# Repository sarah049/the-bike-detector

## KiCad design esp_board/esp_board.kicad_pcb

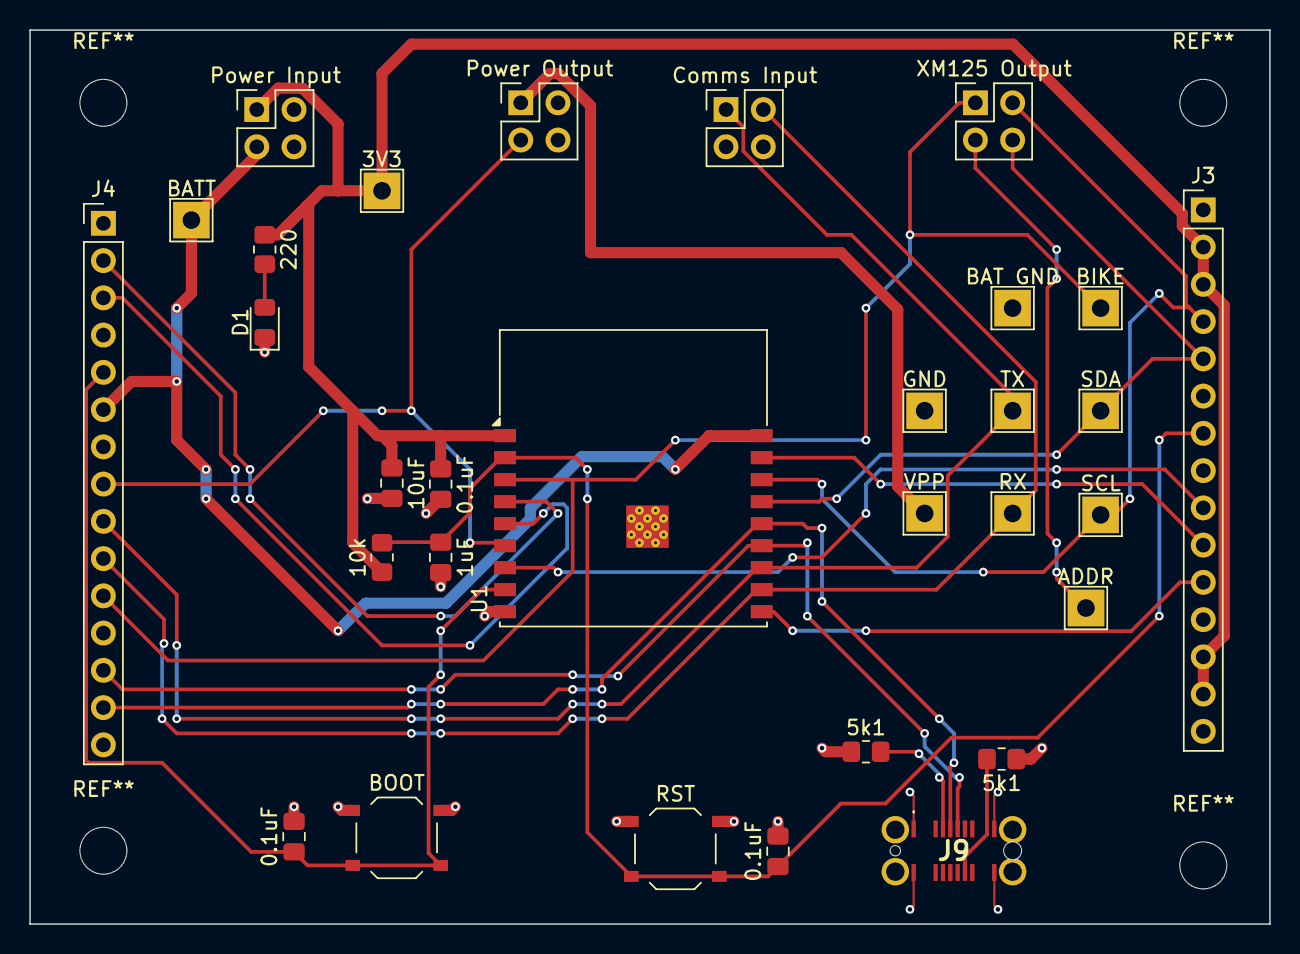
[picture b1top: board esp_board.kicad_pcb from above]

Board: 2 copper layers, 84.5 x 61.0 mm, 31 parts (0 on the bottom side), 23 nets.

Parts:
0.1uF, 0.1uF#2, 0.1uF#3: 0.1uF; C_0805_2012Metric_Pad1.18x1.45mm_HandSolder
1uF: 1uF; C_0805_2012Metric_Pad1.18x1.45mm_HandSolder
3V3: 3V3; TestPoint_THTPad_2.5x2.5mm_Drill1.2mm
5k1, 5k1#2: 5K1; R_0805_2012Metric_Pad1.20x1.40mm_HandSolder
10k: 10k; R_0805_2012Metric_Pad1.20x1.40mm_HandSolder
10uF: 10uF; C_0805_2012Metric_Pad1.18x1.45mm_HandSolder
220: 220; R_0805_2012Metric_Pad1.20x1.40mm_HandSolder
ADDR: ADDR; TestPoint_THTPad_2.5x2.5mm_Drill1.2mm
BAT GND: Bat Ground; TestPoint_THTPad_2.5x2.5mm_Drill1.2mm
BATT: BATT\; TestPoint_THTPad_2.5x2.5mm_Drill1.2mm
BIKE: BIKE; TestPoint_THTPad_2.5x2.5mm_Drill1.2mm
BOOT: SW_Push; SW_Push_1P1T_XKB_TS-1187A
Comms Input: Comms Input; PinHeader_2x02_P2.54mm_Vertical
D1: GREEN; LED_0805_2012Metric_Pad1.15x1.40mm_HandSolder
GND: Ground; TestPoint_THTPad_2.5x2.5mm_Drill1.2mm
J3: Connectors pt. 1; PinHeader_1x15_P2.54mm_Vertical
J4: Connectors pt. 2; PinHeader_1x15_P2.54mm_Vertical
J9: USB4145-03-0170-C; USB4145030170C
Power Input: Power Input; PinHeader_2x02_P2.54mm_Vertical
Power Output: Power Output; PinHeader_2x02_P2.54mm_Vertical
RST: SW_Push; SW_Push_1P1T_XKB_TS-1187A
RX: RX_COM; TestPoint_THTPad_2.5x2.5mm_Drill1.2mm
SCL: XM_I2C_SCL; TestPoint_THTPad_2.5x2.5mm_Drill1.2mm
SDA: XM_I2C_SDA; TestPoint_THTPad_2.5x2.5mm_Drill1.2mm
TX: TX_COM; TestPoint_THTPad_2.5x2.5mm_Drill1.2mm
U1: ESP32-C3-WROOM-02
VPP: VPP; TestPoint_THTPad_2.5x2.5mm_Drill1.2mm
XM125 Output: XM125 Output; PinHeader_2x02_P2.54mm_Vertical

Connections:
+3V3: 0.1uF.1, 3V3.1, 10k.1, 10uF.1, 220.1, J3.2, J3.3, J3.13, J3.14, Power Input.1, U1.1 (3V3)
+BATT: BATT.1, J4.6, Power Input.3, U1.18 (IO0)
/ADDR: ADDR.1, XM125 Output.3
/BIKE: BIKE.1, J4.11, U1.3 (IO4), XM125 Output.1
/CHIP_PU: 0.1uF#2.1, 1uF.1, 10k.2, J3.7, RST.2, U1.2 (EN)
/COMMS_EN: J4.8, Power Output.3, U1.6 (IO7)
/GPIO1: J3.10, U1.17 (IO1)
/GPIO5: J4.2, U1.4 (IO5)
/GPIO6: J4.3, U1.5 (IO6)
/GPIO8: J3.9, U1.7 (IO8)
/GPIO9: 0.1uF#3.1, BOOT.2, J4.5, U1.8 (IO9)
/GPIO10: J3.11, U1.10 (IO10)
/GPIO18: J4.13, J9.A7 (DN1), U1.13 (IO18)
/GPIO19: J4.14, J9.A6 (DP1), U1.14 (IO19)
/RX_COMMS: Comms Input.2, J4.10, RX.1, U1.11 (IO20/RXD)
/TX_COMMS: Comms Input.1, J4.9, TX.1, U1.12 (IO21/TXD)
/XM_I2C_SCL: J3.4, SCL.1, U1.16 (IO2), XM125 Output.2
/XM_I2C_SDA: J3.5, SDA.1, U1.15 (IO3), XM125 Output.4
GND: 0.1uF.2, 0.1uF#2.2, 0.1uF#3.2, 1uF.2, 5k1.1, 5k1#2.1, 10uF.2, BAT GND.1, BOOT.1, D1.1 (K), GND.1, J3.1, J3.6, J3.8, J3.12, J3.15, J4.1, J4.4, J4.7, J4.12, J4.15, J9.A1 (GND_1), J9.A12 (GND_2), J9.B1 (GND_3), J9.B12 (GND_4), Power Input.2, Power Output.2, RST.1, U1.9 (GND), U1.19 (GND)
unnamed: 220.2, D1.2 (A)
unnamed: 5k1.2, J9.A5 (CC1)
unnamed: 5k1#2.2, J9.B5 (CC2)
VPP: Power Output.1, VPP.1

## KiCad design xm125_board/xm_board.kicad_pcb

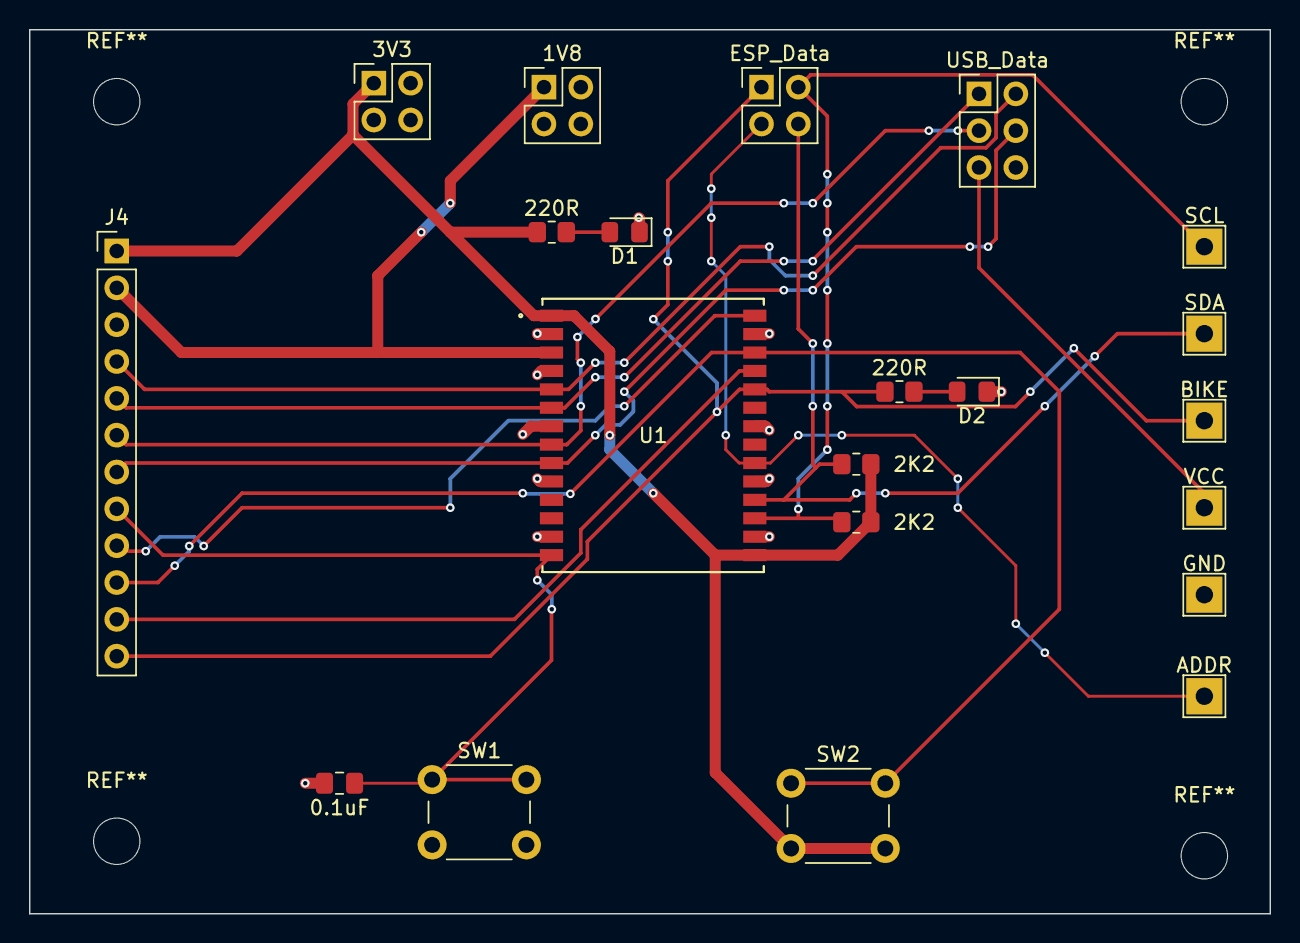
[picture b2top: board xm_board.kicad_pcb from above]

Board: 2 copper layers, 85.5 x 61.0 mm, 21 parts (0 on the bottom side), 18 nets.

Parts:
0.1uF: 0.1uF; C_0805_2012Metric_Pad1.18x1.45mm_HandSolder
1V8: 1V8; PinHeader_2x02_P2.54mm_Vertical
2K2: 2K2; R_0805_2012Metric_Pad1.20x1.40mm_HandSolder
3V3: 3V3; PinHeader_2x02_P2.54mm_Vertical
220R, 220R#2: 220; R_0805_2012Metric_Pad1.20x1.40mm_HandSolder
D1, D2: GREEN; LED_0805_2012Metric_Pad1.15x1.40mm_HandSolder
ESP_Data: ESP_Data; PinHeader_2x02_P2.54mm_Vertical
J4: Conn_01x12_Pin; PinHeader_1x12_P2.54mm_Vertical
R1: 2K2; R_0805_2012Metric_Pad1.20x1.40mm_HandSolder
SCL: SCL; TestPoint_THTPad_2.5x2.5mm_Drill1.2mm
SW1: SW_Push; SW_PUSH_6mm_H8.5mm
SW2: SW_Boot; SW_PUSH_6mm_H8.5mm
TP2: SDA; TestPoint_THTPad_2.5x2.5mm_Drill1.2mm
TP3: BIKE; TestPoint_THTPad_2.5x2.5mm_Drill1.2mm
TP4: VCC; TestPoint_THTPad_2.5x2.5mm_Drill1.2mm
TP5: GND; TestPoint_THTPad_2.5x2.5mm_Drill1.2mm
TP6: ADDR; TestPoint_THTPad_2.5x2.5mm_Drill1.2mm
U1: XM125; XM125_ACC
USB_Data: USB_Data; PinHeader_2x03_P2.54mm_Vertical

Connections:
+1V8: 1V8.1, J4.2, U1.3 (1V8)
+3V3: 2K2.2, 3V3.1, 220R#2.1, J4.1, R1.2, SW2.2, U1.1 (VIN), U1.15 (WAKE_UP)
/ADDR: ESP_Data.3, TP6.1, U1.20 (I2C_ADDRESS)
/BOOT: J4.10, SW2.1, U1.26 (MISC_GPIO2_BOOT0)
/CTS: J4.7, U1.9 (UART_RTS), USB_Data.4
/GPIO0: 220R.1, ESP_Data.1, J4.12, TP3.1, U1.24 (MISC_GPIO0)
/GPIO1: J4.11, U1.25 (MISC_GPIO1)
/INT: J4.9, U1.28 (MCU_INT)
/RESET: 0.1uF.1, J4.8, SW1.1, U1.14 (NRESET)
/RTS: J4.6, U1.8 (UART_CTS), USB_Data.3
/RX: J4.4, U1.5 (UART_TX), USB_Data.2
/SCL: 2K2.1, ESP_Data.2, SCL.1, U1.17 (I2C_SCL)
/SDA: ESP_Data.4, R1.1, TP2.1, U1.18 (I2C_SDA)
/TX: J4.5, U1.6 (UART_RX), USB_Data.1
GND: 0.1uF.2, 1V8.2, 3V3.2, D1.1 (K), D2.1 (K), J4.3, SW1.2, TP5.1, U1.2 (GROUND), U1.4 (GROUND), U1.7 (GROUND), U1.10 (GROUND), U1.13 (GROUND), U1.16 (GROUND), U1.19 (GROUND), U1.22 (GROUND), U1.27 (GROUND), USB_Data.6
unnamed: 220R#2.2, D1.2 (A)
unnamed: 220R.2, D2.2 (A)
VCC: TP4.1, USB_Data.5

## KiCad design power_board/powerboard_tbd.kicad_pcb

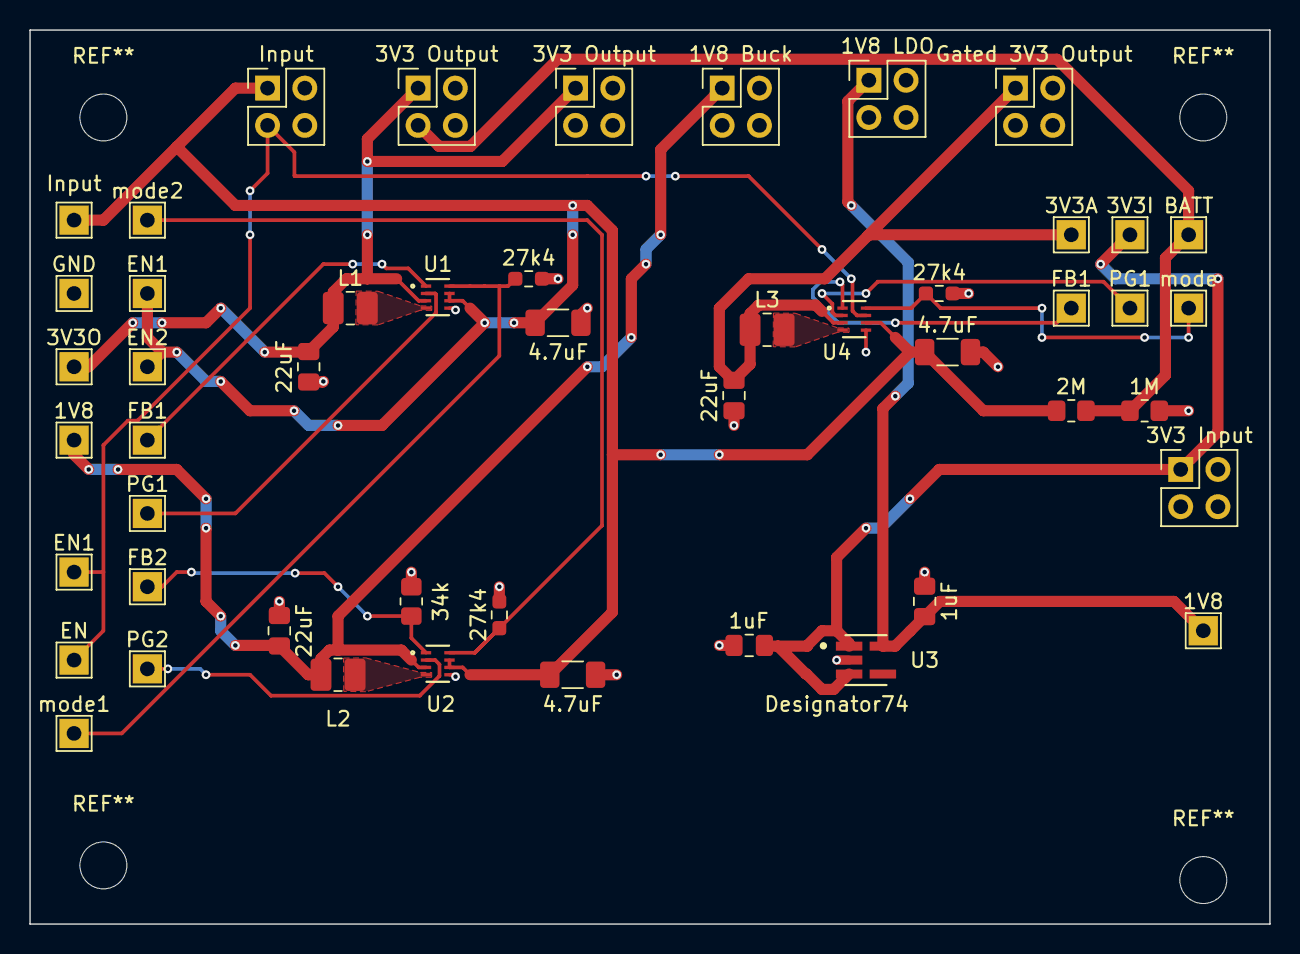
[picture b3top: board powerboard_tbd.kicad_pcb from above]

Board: 2 copper layers, 84.5 x 61.0 mm, 49 parts (0 on the bottom side), 21 nets.

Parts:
1M: 1M; R_0805_2012Metric_Pad1.20x1.40mm_HandSolder
1V8: Output_1V8_LDO; TestPoint_THTPad_2.0x2.0mm_Drill1.0mm
1V8 Buck: 1V8 Buck; PinHeader_2x02_P2.54mm_Vertical
1V8 LDO: 1V8 LDO; PinHeader_2x02_P2.54mm_Vertical
1V8#2: Output_1V8_Buck; TestPoint_THTPad_2.0x2.0mm_Drill1.0mm
1uF, 1uF#2: 1uF; C_0805_2012Metric_Pad1.18x1.45mm_HandSolder
2M: 2M; R_0805_2012Metric_Pad1.20x1.40mm_HandSolder
3V3 Input: 3V3 Input; PinHeader_2x02_P2.54mm_Vertical
3V3 Output, 3V3 Output#2: 3V3 Output; PinHeader_2x02_P2.54mm_Vertical
3V3A: Gated 3V3; TestPoint_THTPad_2.0x2.0mm_Drill1.0mm
3V3I: Input_3V3; TestPoint_THTPad_2.0x2.0mm_Drill1.0mm
3V3O: Output_3V3; TestPoint_THTPad_2.0x2.0mm_Drill1.0mm
4.7uF, 4.7uF#2, 4.7uF#3: 4.7uF; C_1206_3216Metric_Pad1.33x1.80mm_HandSolder
22uF, 22uF#2, 22uF#3: 22uF; C_0805_2012Metric_Pad1.18x1.45mm_HandSolder
27k4, 27k4#2, 27k4#3: 27.4k; R_0603_1608Metric_Pad0.98x0.95mm_HandSolder
34k: 34k; R_0805_2012Metric_Pad1.20x1.40mm_HandSolder
BATT: Output_BATT; TestPoint_THTPad_2.0x2.0mm_Drill1.0mm
EN: EN_Comms; TestPoint_THTPad_2.0x2.0mm_Drill1.0mm
EN1: EN1; TestPoint_THTPad_2.0x2.0mm_Drill1.0mm
EN2: EN2; TestPoint_THTPad_2.0x2.0mm_Drill1.0mm
FB1, FB1#2: FB1; TestPoint_THTPad_2.0x2.0mm_Drill1.0mm
FB2: FB2; TestPoint_THTPad_2.0x2.0mm_Drill1.0mm
GND: GND; TestPoint_THTPad_2.0x2.0mm_Drill1.0mm
Gated 3V3 Output: Gated 3V3 Output; PinHeader_2x02_P2.54mm_Vertical
GatedEN1: EN1; TestPoint_THTPad_2.0x2.0mm_Drill1.0mm
Input: Input; TestPoint_THTPad_2.0x2.0mm_Drill1.0mm
Input#2: Input; PinHeader_2x02_P2.54mm_Vertical
L1, L2, L3: 2.2uH; L_1008_2520Metric_Pad1.43x2.20mm_HandSolder
PG1, PG1#2: PG1; TestPoint_THTPad_2.0x2.0mm_Drill1.0mm
PG2: PG2; TestPoint_THTPad_2.0x2.0mm_Drill1.0mm
U1: 3V3 Buck; SOT5X3-8_DRL_TEX
U2: 1V8 Buck; SOT5X3-8_DRL_TEX
U3: 1V8 LDO; DBV0005A-IPC_A
U4: Gated 3V3 Buck; SOT5X3-8_DRL_TEX
mode, mode1: mode1; TestPoint_THTPad_2.0x2.0mm_Drill1.0mm
mode2: mode2; TestPoint_THTPad_2.0x2.0mm_Drill1.0mm

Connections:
+3.3VA: 3V3A.1, 22uF#2.2, Gated 3V3 Output.1, L3.1, U4.3 (VOS)
+3.3VP: 1uF#2.2, 3V3 Input.1, 3V3I.1, U3.1 (IN), U3.3 (EN)
+3V3: 3V3 Output.1, 3V3 Output#2.1, 3V3O.1, 22uF#3.2, L1.1, U1.3 (VOS)
+BATT: 1M.1, 2M.2, 3V3 Output.3, BATT.1
/EN: EN.1, GatedEN1.1, Input#2.3, U4.7 (EN)
GND: 1M.2, 1V8 Buck.2, 1V8 LDO.2, 1uF.1, 1uF#2.1, 3V3 Input.2, 3V3 Output.2, 3V3 Output#2.2, 4.7uF.2, 4.7uF#2.2, 4.7uF#3.2, 22uF.1, 22uF#2.1, 22uF#3.1, 27k4.2, 27k4#2.2, 27k4#3.2, 34k.1, GND.1, Gated 3V3 Output.2, Input#2.2, U1.5 (GND), U2.5 (GND), U3.2 (GND), U4.5 (GND)
unnamed: FB1.1, U1.1 (FB/VSET)
unnamed: 27k4.1, U1.8 (MODE/S-CONF), mode1.1
unnamed: PG1#2.1, U1.2 (PG)
unnamed: L1.2, U1.4 (SW)
unnamed: 34k.2, FB2.1, U2.1 (FB/VSET)
unnamed: 27k4#2.1, U2.8 (MODE/S-CONF), mode2.1
unnamed: PG2.1, U2.2 (PG)
unnamed: L2.2, U2.4 (SW)
unnamed: FB1#2.1, U4.1 (FB/VSET)
unnamed: 27k4#3.1, U4.8 (MODE/S-CONF), mode.1
unnamed: PG1.1, U4.2 (PG)
unnamed: L3.2, U4.4 (SW)
VDDA: 1V8 Buck.1, 1V8#2.1, 22uF.2, L2.1, U2.3 (VOS)
VDDF: 1V8.1, 1V8 LDO.1, 1uF.2, U3.5 (OUT)
VPP: 2M.1, 4.7uF.1, 4.7uF#2.1, 4.7uF#3.1, EN1.1, EN2.1, Input.1, Input#2.1, U1.6 (VIN), U1.7 (EN), U2.6 (VIN), U2.7 (EN), U4.6 (VIN)

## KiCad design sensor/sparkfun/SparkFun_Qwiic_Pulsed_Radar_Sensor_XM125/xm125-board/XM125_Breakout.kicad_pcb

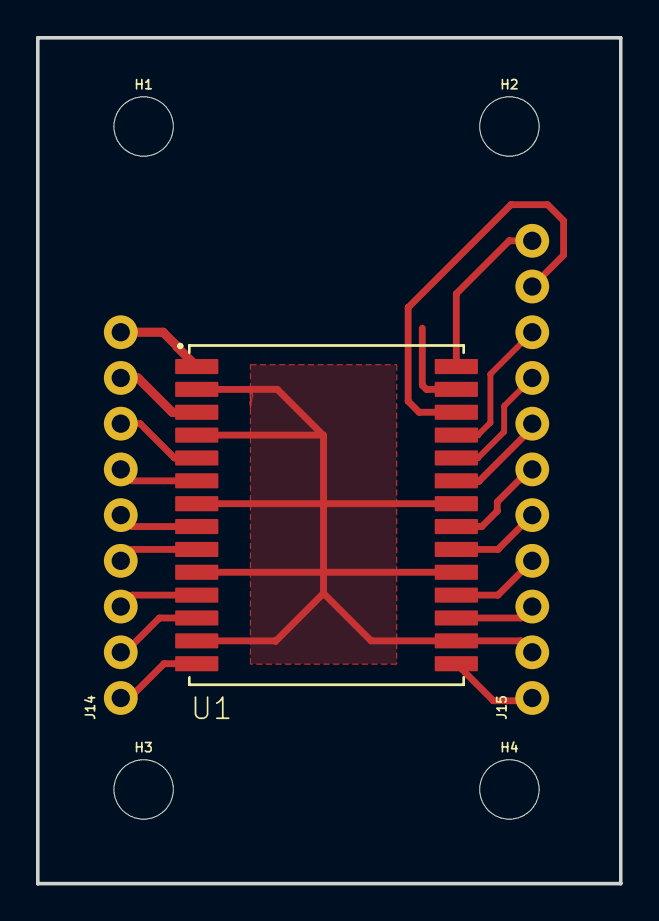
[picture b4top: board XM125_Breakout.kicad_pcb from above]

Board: 2 copper layers, 32.4 x 47.0 mm, 8 parts (0 on the bottom side), 20 nets.

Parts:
FRAME2: FRAME-LETTER; CREATIVE_COMMONS
H1, H2, H3, H4: STAND-OFF
J14: 1X09_NO_SILK
J15: 1X11_NO_SILK
U1: XM125; XM125_ACC

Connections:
1.8V: J14.8, U1.3
3.3V: J14.9, U1.1
CH340-CTS: J14.4, U1.9
CH340-RTS: J14.5, U1.8
CH340-RX: J14.7, U1.5
CH340-TX: J14.6, U1.6
DEBUG_UART-RX: J15.6, U1.21
DEBUG_UART-TX: J15.7, U1.23
GND: J15.2, U1.2, U1.4, U1.7, U1.10, U1.13, U1.16, U1.19, U1.22, U1.27
SCL: J15.3, U1.17
SDA: J15.4, U1.18
SWD_CLK: J14.2, U1.12
SWD_IO: J14.3, U1.11
WAKE_UP: J15.1, U1.15
XM125_GPIO0: J15.8, U1.24
XM125_GPIO1: J15.9, U1.25
XM125_GPIO2/BOOT0: J15.10, U1.26
XM125_I2C_ADDRESS: J15.5, U1.20
~XM125_INT: J15.11, U1.28
~XM125_RESET: J14.1, U1.14

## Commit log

2025-11-01 tbd up
